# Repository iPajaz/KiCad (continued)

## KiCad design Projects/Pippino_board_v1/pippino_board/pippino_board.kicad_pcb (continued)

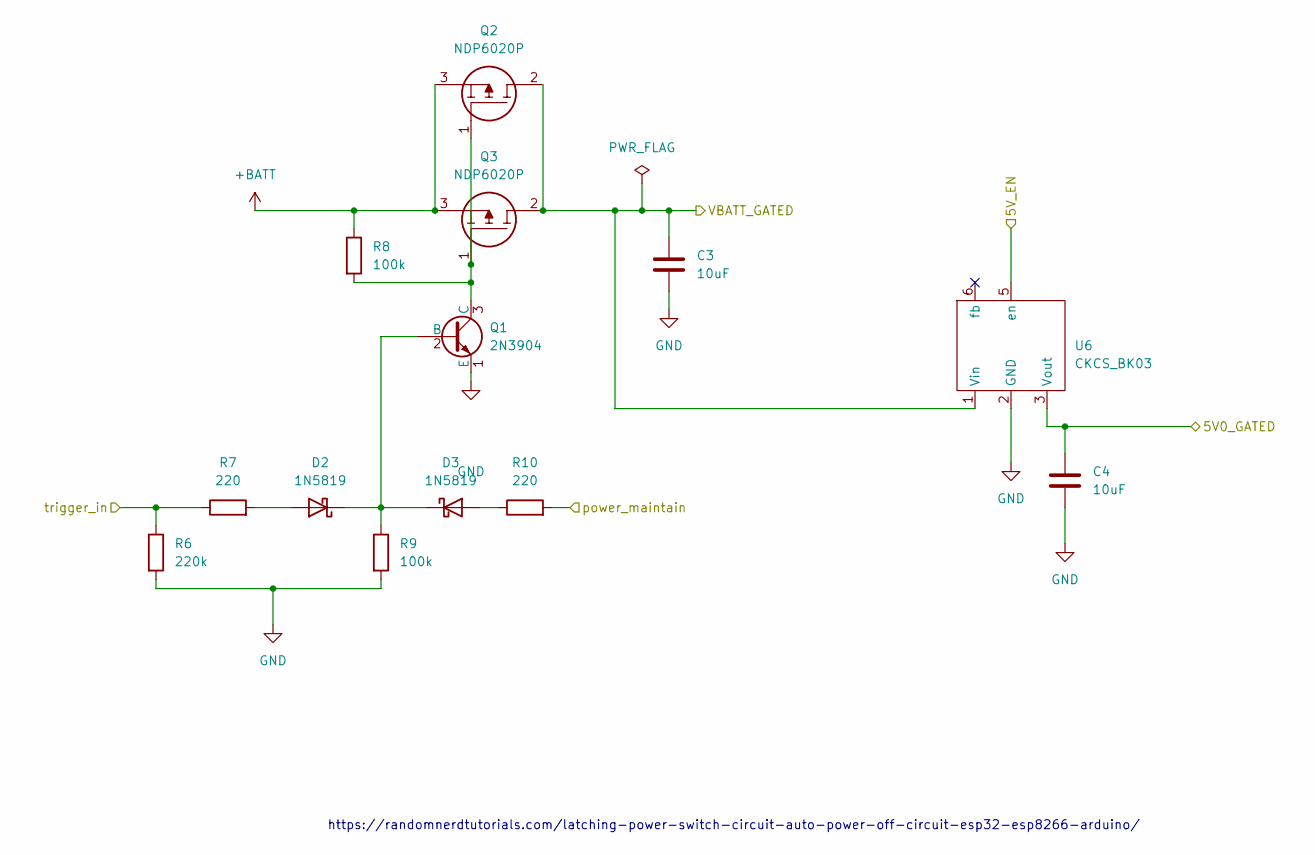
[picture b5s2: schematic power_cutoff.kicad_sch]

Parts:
C3, C4: 10uF; C_0805_2012Metric
D2, D3: 1N5819; D_SMA
Q1: 2N3904; 2N3904_SOT-23
Q2, Q3: NDP6020P; TO254P470X1016X2019-3P; Manufacturer_Part_Number NDP6020P; Mouser Part Number 512-NDP6020P
R6: 220k; R_1206_3216Metric
R7, R10: 220; R_1206_3216Metric
R8, R9: 100k; R_1206_3216Metric
U6: CKCS_BK03; CKCS-BK03

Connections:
5V_GATED: C4.1, U6.3 (Vout); also elsewhere on the board
+BATT: Q2.3, Q3.3, R8.1; also elsewhere on the board
/VBATT_maintain: R10.2; also elsewhere on the board
/VBATT_trigger: R6.1, R7.1; also elsewhere on the board
/power_cutoff/5V_EN: U6.5 (en)
GND: C3.2, C4.2, Q1.1 (E), R6.2, R9.2, U6.2 (GND); also elsewhere on the board
unnamed: D2.1 (K), D3.1 (K), Q1.2 (B), R9.1
unnamed: D2.2 (A), R7.2
unnamed: D3.2 (A), R10.1
unnamed: Q1.3 (C), Q2.1, Q3.1, R8.2
VBATT_GATED: C3.1, Q2.2, Q3.2, U6.1 (Vin); also elsewhere on the board

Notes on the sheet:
https://randomnerdtutorials.com/latching-power-switch-circuit-auto-power-off-circuit-esp32-esp8266-arduino/

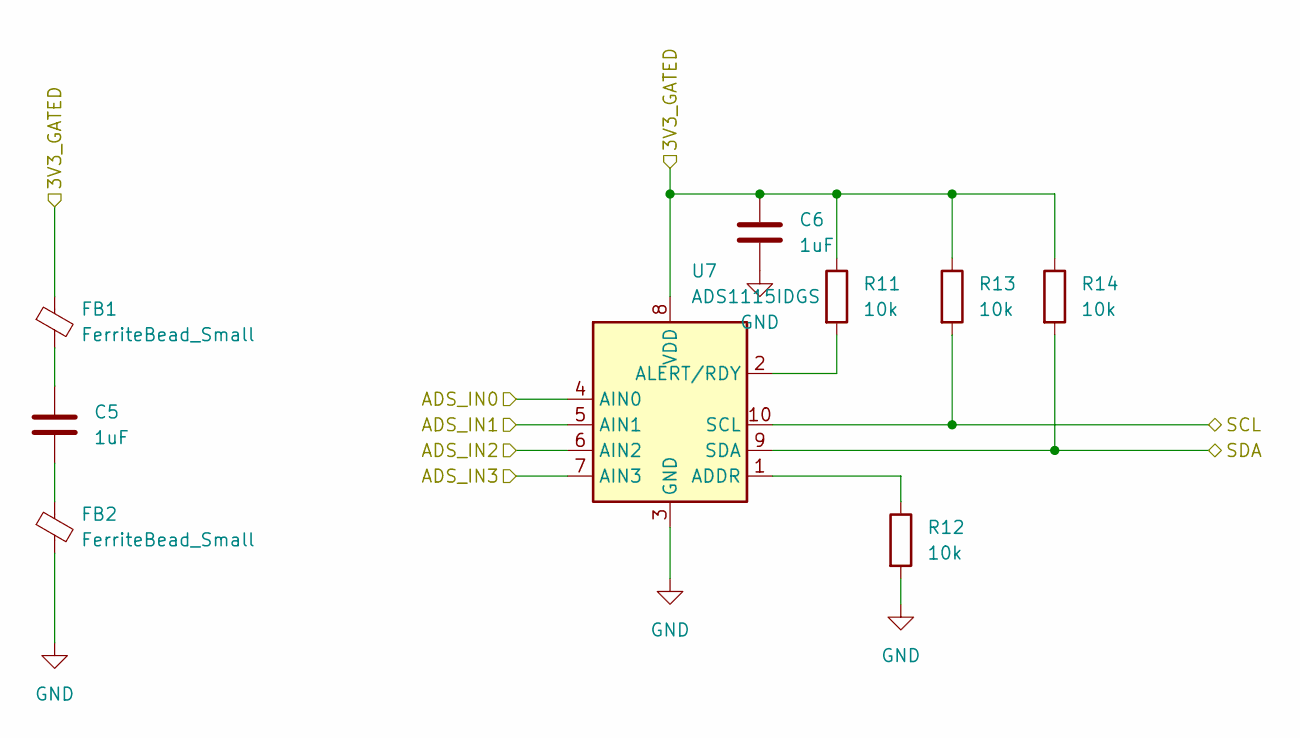
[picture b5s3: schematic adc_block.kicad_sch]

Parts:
C5, C6: 1uF; C_0805_2012Metric
FB1, FB2: FerriteBead_Small; R_1206_3216Metric
R11, R12, R13, R14: 10k; R_1206_3216Metric
U7: ADS1115IDGS; TSSOP-10_3x3mm_P0.5mm

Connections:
3V3_ESP32: C6.1, FB1.1, R11.1, R13.1, R14.1, U7.8 (VDD); also elsewhere on the board
/ADC/ADS_IN1: U7.5 (AIN1); also elsewhere on the board
/ADC/ADS_IN3: U7.7 (AIN3)
/ADS0: U7.4 (AIN0); also elsewhere on the board
/ADS2: U7.6 (AIN2); also elsewhere on the board
/SCL: R13.2, U7.10 (SCL); also elsewhere on the board
/SDA: R14.2, U7.9 (SDA); also elsewhere on the board
GND: C6.2, FB2.2, R12.2, U7.3 (GND); also elsewhere on the board
unnamed: C5.1, FB1.2
unnamed: C5.2, FB2.1
unnamed: R11.2, U7.2 (ALERT/RDY)
unnamed: R12.1, U7.1 (ADDR)

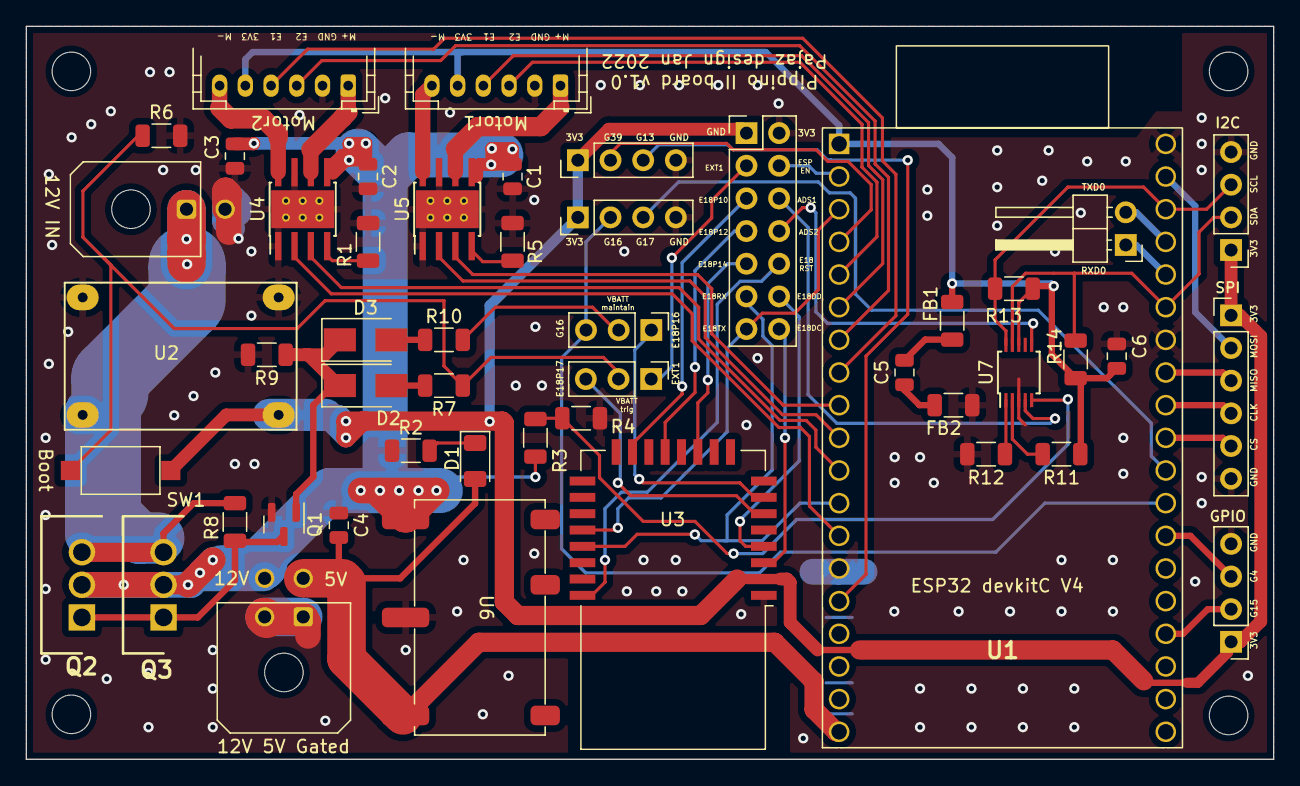
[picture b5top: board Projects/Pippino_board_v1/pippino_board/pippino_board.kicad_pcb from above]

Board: 2 copper layers, 97.0 x 57.0 mm, 53 parts (0 on the bottom side), 60 nets.

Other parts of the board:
C1, C2: 0.1uF; C_0805_2012Metric
MH1, MH2, MH3, MH4: MountingHole_3mm
R1, R5: 18k; R_1206_3216Metric
U4, U5: DRV8871DDA; Texas_HTSOP-8-1EP_3.9x4.9mm_P1.27mm_EP2.95x4.9mm_Mask2.4x3.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

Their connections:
/M1+: U4.6 (OUT1); also elsewhere on the board
/M1-: U4.8 (OUT2); also elsewhere on the board
/M1PWM1: U4.3 (IN1); also elsewhere on the board
/M1PWM2: U4.2 (IN2); also elsewhere on the board
/M2+: U5.6 (OUT1); also elsewhere on the board
/M2-: U5.8 (OUT2); also elsewhere on the board
/M2PWM1: U5.3 (IN1); also elsewhere on the board
/M2PWM2: U5.2 (IN2); also elsewhere on the board
GND: C1.2, C2.2, R1.2, R5.2, U4.1 (GND), U4.7 (GND), U4.9 (GND), U5.1 (GND), U5.7 (GND), U5.9 (GND); also elsewhere on the board
unnamed: R1.1, U4.4 (ILIM)
unnamed: R5.1, U5.4 (ILIM)
VBATT_GATED: C1.1, C2.1, U4.5 (VM), U5.5 (VM); also elsewhere on the board

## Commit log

2022-04-04 first commit with pippino and garden boards
2022-04-08 work
2023-04-07 added pippino board v2
2023-04-27 work on pippino board v2
2023-04-27 work on pcb
2023-04-28 work on pippino II board v2.1
2023-04-30 changed 5v buck to smaller one
2023-10-18 moved to ubu 22, updated pippino v2.1
